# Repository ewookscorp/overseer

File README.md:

# Overseer the homeautomation project
Building homeautomation overseer backend, harware and other needed stuff. Initial with build Temperature and humidity sensor from ESP2866
See more from [Wiki](https://github.com/taiffu/overseer/wiki/Overseer-the-homeautomation-system)

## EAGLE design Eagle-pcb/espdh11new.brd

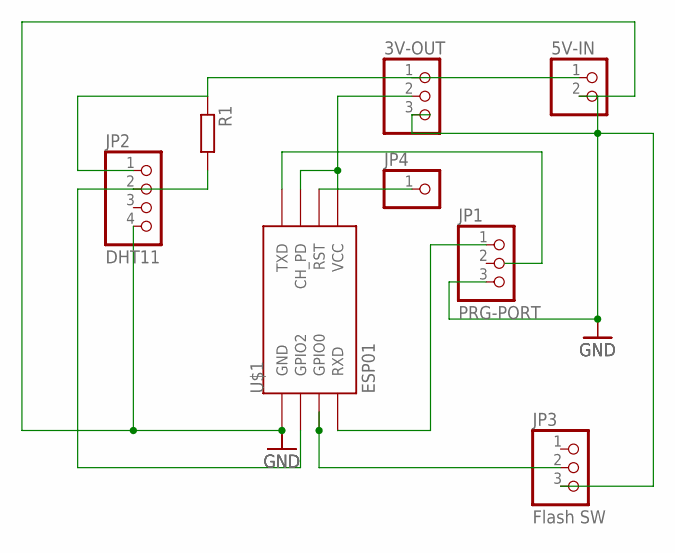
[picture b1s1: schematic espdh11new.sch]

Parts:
3V-OUT: PINHD-1X3; 1X03
5V-IN: PINHD-1X2; 1X02
JP1: PRG-PORT; 1X03
JP2: DHT11; 1X04
JP3: Flash SW; 1X03/90
JP4: PINHD-1X1; 1X01
R1: R-EU_0204/5; 0204/5
U$1: ESP01

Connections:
5V: 3V-OUT.1, 5V-IN.1, JP2.1, R1.1
GND: 3V-OUT.3, 5V-IN.2, JP1.3, JP2.4, JP3.3, U$1.GND
GPIO2: JP2.2, R1.2, U$1.GPIO2
unnamed: JP3.2, U$1.GPIO0
unnamed: 3V-OUT.2, U$1.CH_PD, U$1.VCC
RESET: JP4.1, U$1.RST
RXD: JP1.1, U$1.RX (RXD)
TXD: U$1.TX (TXD)

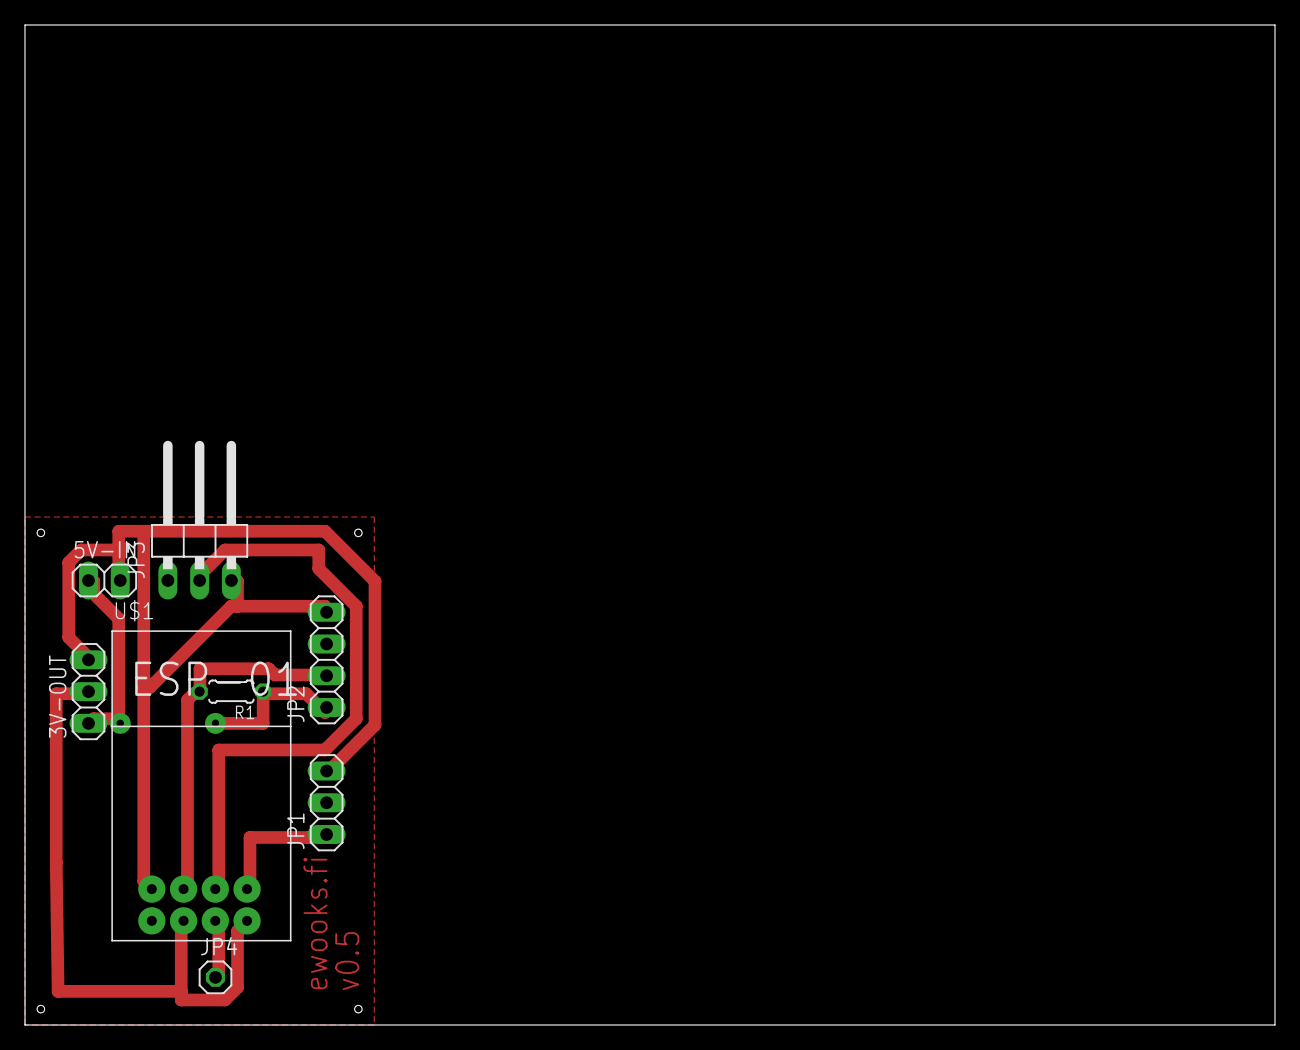
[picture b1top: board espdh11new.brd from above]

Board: 2 copper layers, 100.0 x 80.0 mm, 8 parts (0 on the bottom side), 7 nets.

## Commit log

2016-08-21 Inital commit
2016-08-21 images
2016-08-22 Tools and firmwares
2016-08-22 ReadMe update
